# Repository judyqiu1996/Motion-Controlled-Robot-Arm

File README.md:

# Motion Controlled Robot Arm

1. Designed a circuit and PCB board receiving the sensor information from arm by Bluetooth and controlling the action of the robot.

2. Used I2C and SPI methods to communicate between chip and software.

3. Devised an algorithm of filtering and processing sensor data, manipulating robot arm in 3 Axis, including pitch and roll axes.

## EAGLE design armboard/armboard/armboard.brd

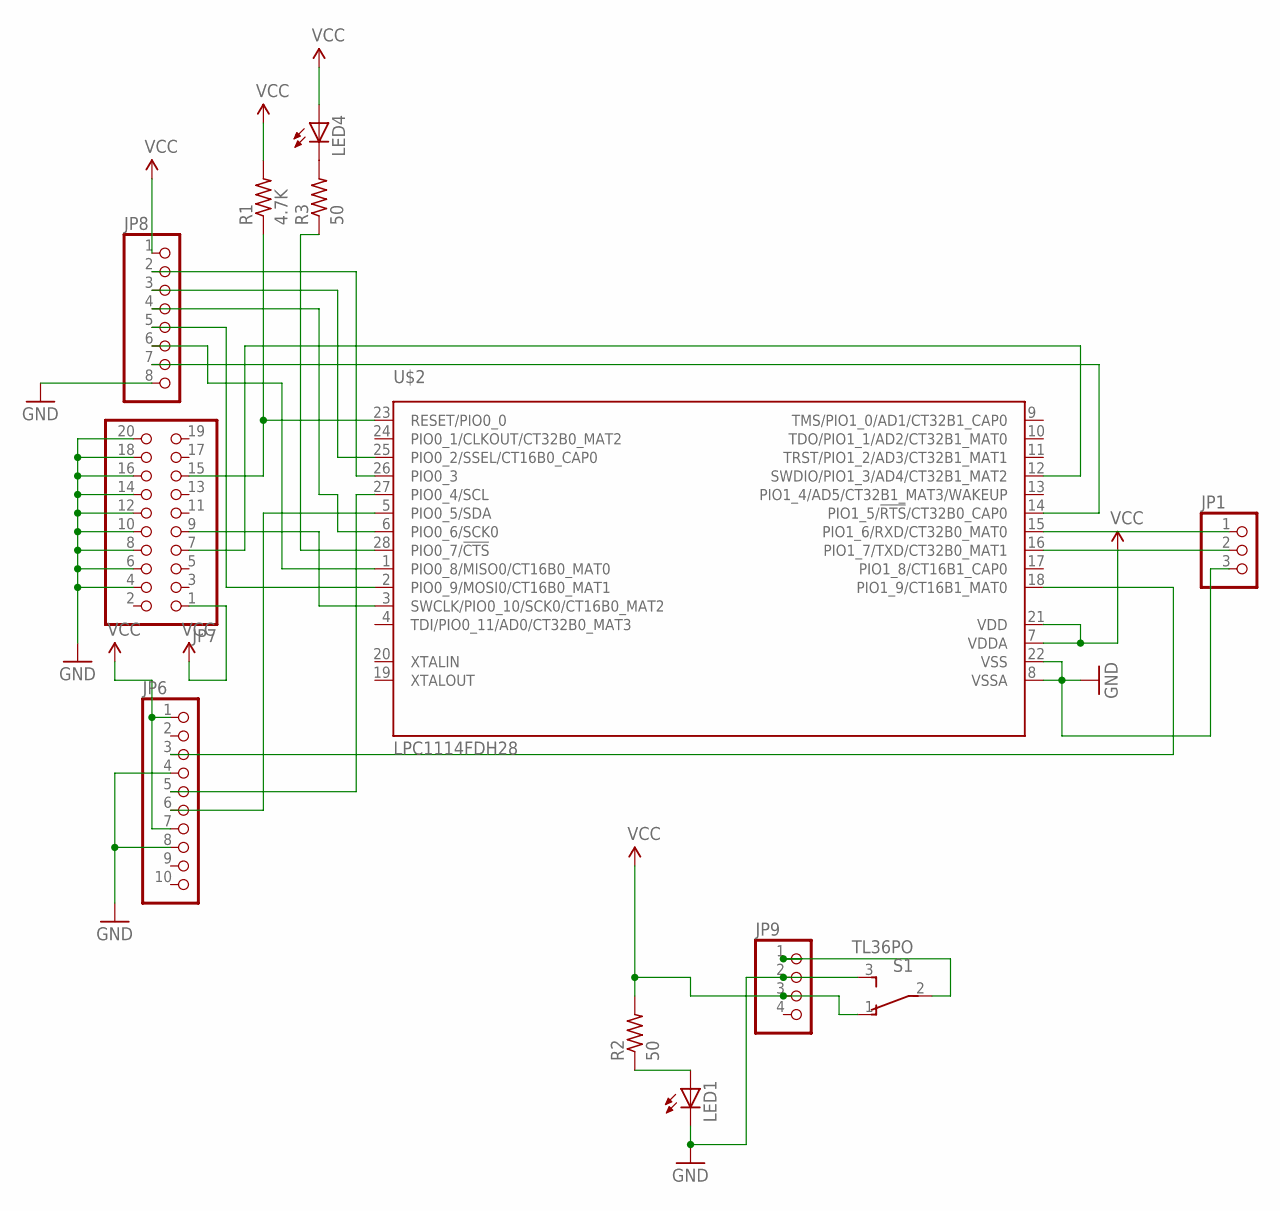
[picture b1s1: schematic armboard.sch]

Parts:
JP1: PINHD-1X3; 1X03
JP6: PINHD-1X10; 1X10
JP7: PINHD-2X10; 2X10
JP8: PINHD-1X8; 1X08
JP9: PINHD-1X4; 1X04
LED1, LED4: LED5MM
R1: 4.7K; 0207/10
R2, R3: 50; 0207/10
S1: TL36PO; TL3XPO
U$2: LPC1114FDH28; SOT361-1

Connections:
GND: JP1.3, JP6.4, JP6.8, JP7.4, JP7.6, JP7.8, JP7.10, JP7.12, JP7.14, JP7.16, JP7.18, JP7.20, JP8.8, JP9.2, LED1.K (C), S1.3 (S), U$2.8 (VSSA), U$2.22 (VSS)
unnamed: JP7.15, R1.1, U$2.23 (RESET/PIO0_0)
unnamed: JP9.1, S1.2
unnamed: LED4.K (C), R3.2
unnamed: R3.1, U$2.28 (PIO0_7/!CTS!)
unnamed: JP7.9, U$2.3 (SWCLK/PIO0_10/SCK0/CT16B0_MAT2)
unnamed: JP8.6, U$2.1 (PIO0_8/MISO0/CT16B0_MAT0)
unnamed: JP1.1, U$2.15 (PIO1_6/RXD/CT32B0_MAT0)
unnamed: JP8.5, U$2.2 (PIO0_9/MOSI0/CT16B0_MAT1)
unnamed: JP8.3, U$2.25 (PIO0_2/SSEL/CT16B0_CAP0)
unnamed: JP6.6, U$2.5 (PIO0_5/SDA)
unnamed: JP8.2, U$2.26 (PIO0_3)
unnamed: JP1.2, U$2.16 (PIO1_7/TXD/CT32B0_MAT1)
unnamed: JP6.3, U$2.18 (PIO1_9/CT16B1_MAT0)
unnamed: JP8.4, U$2.6 (PIO0_6/SCK0)
unnamed: LED1.A, R2.1
unnamed: JP8.7, U$2.14 (PIO1_5/!RTS!/CT32B0_CAP0)
unnamed: JP6.5, U$2.27 (PIO0_4/SCL)
unnamed: JP7.7, U$2.12 (SWDIO/PIO1_3/AD4/CT32B1_MAT2)
VCC: JP6.1, JP6.7, JP7.1, JP8.1, JP9.3, LED4.A, R1.2, R2.2, S1.1 (O), U$2.7 (VDDA), U$2.21 (VDD)

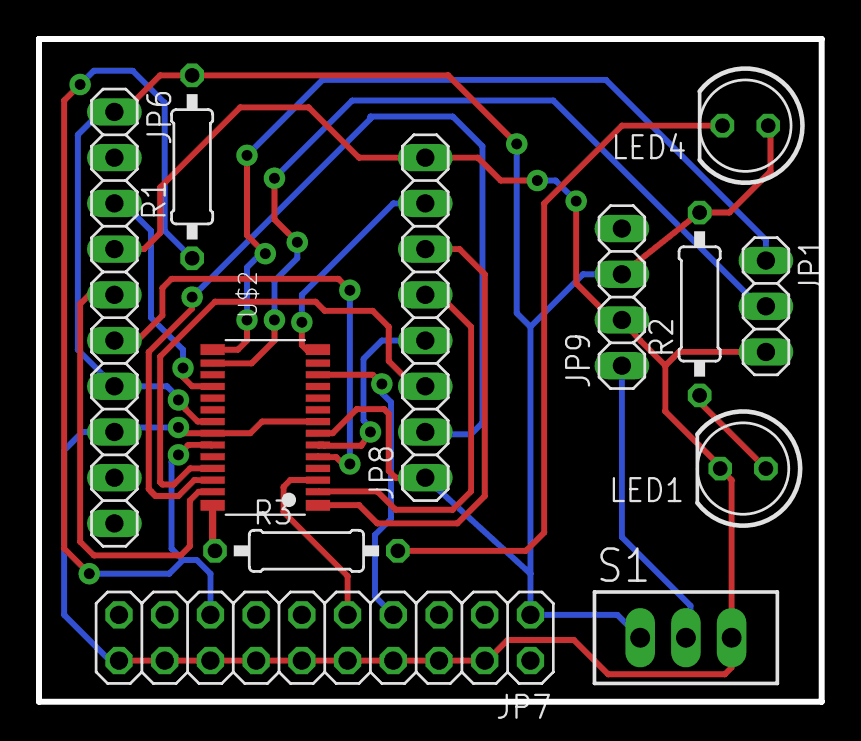
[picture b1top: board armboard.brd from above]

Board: 2 copper layers, 43.5 x 36.8 mm, 12 parts (0 on the bottom side), 20 nets.

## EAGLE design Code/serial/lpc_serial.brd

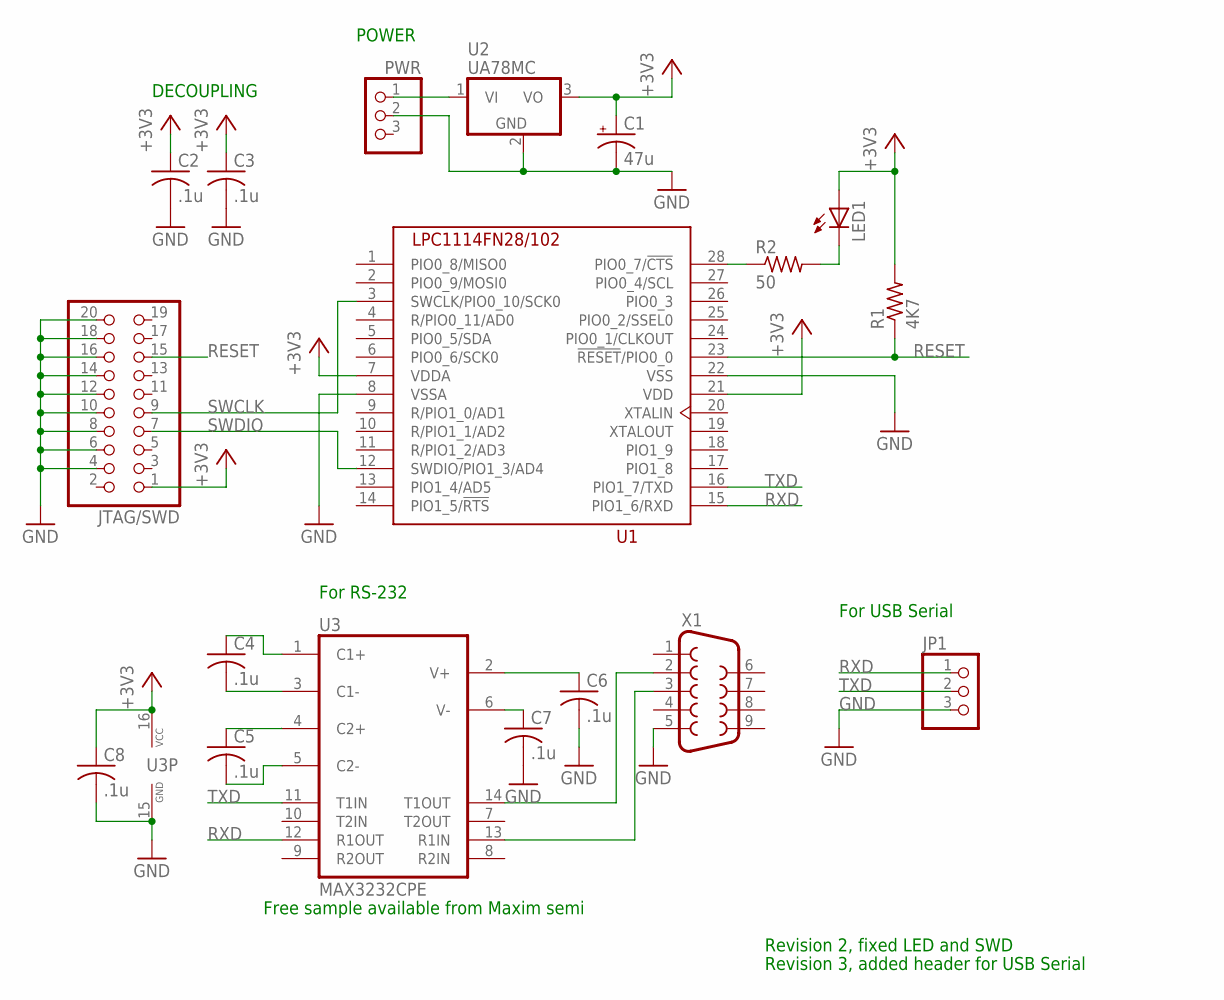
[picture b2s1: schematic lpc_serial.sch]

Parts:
C1: 47u; E3,5-8
C2, C3, C4, C5, C6, C7, C8: .1u; C050-024X044
JP1: PINHD-1X3; 1X03
JTAG/SWD: PINHD-2X10; 2X10
LED1: LED10MM
PWR: PINHD-1X3; 1X03
R1: 4K7; 0207/10
R2: 50; 0207/10
U1: LPC1114FN28/102; DIL28-6
U2: UA78MC; TO220V
U3: MAX3232CPE; DIL16
X1: F09H

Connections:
+3V3: C1.+, C2.1, C3.1, C8.1, JTAG/SWD.1, LED1.A, R1.2, U1.7 (VDDA), U1.21 (VDD), U2.3 (VO), U3.16 (VCC)
GND: C1.-, C2.2, C3.2, C6.2, C7.2, C8.2, JP1.3, JTAG/SWD.4, JTAG/SWD.6, JTAG/SWD.8, JTAG/SWD.10, JTAG/SWD.12, JTAG/SWD.14, JTAG/SWD.16, JTAG/SWD.18, JTAG/SWD.20, PWR.2, U1.8 (VSSA), U1.22 (VSS), U2.2 (GND), U3.15 (GND), X1.5
unnamed: LED1.K (C), R2.2
unnamed: PWR.1, U2.1 (VI)
unnamed: R2.1, U1.28 (PIO0_7/!CTS)
unnamed: U3.14 (T1OUT), X1.2
unnamed: U3.13 (R1IN), X1.3
unnamed: C4.1, U3.1 (C1+)
unnamed: C4.2, U3.3 (C1-)
unnamed: C5.1, U3.4 (C2+)
unnamed: C5.2, U3.5 (C2-)
unnamed: C6.1, U3.2 (V+)
unnamed: C7.1, U3.6 (V-)
RESET: JTAG/SWD.15, R1.1, U1.23 (!RESET!/PIO0_0)
RXD: JP1.1, U1.15 (PIO1_6/RXD), U3.12 (R1OUT)
SWCLK: JTAG/SWD.9, U1.3 (SWCLK/PIO0_10/SCK0)
SWDIO: JTAG/SWD.7, U1.12 (SWDIO/PIO1_3/AD4)
TXD: JP1.2, U1.16 (PIO1_7/TXD), U3.11 (T1IN)

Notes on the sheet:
POWER
DECOUPLING
Revision 2, fixed LED and SWD
Free sample available from Maxim semi
For USB Serial
For RS-232
Revision 3, added header for USB Serial

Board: 2 copper layers, 18 parts (0 on the bottom side), 18 nets, no tracks yet.

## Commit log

2017-09-12 Motion Controlled Robot Arm
